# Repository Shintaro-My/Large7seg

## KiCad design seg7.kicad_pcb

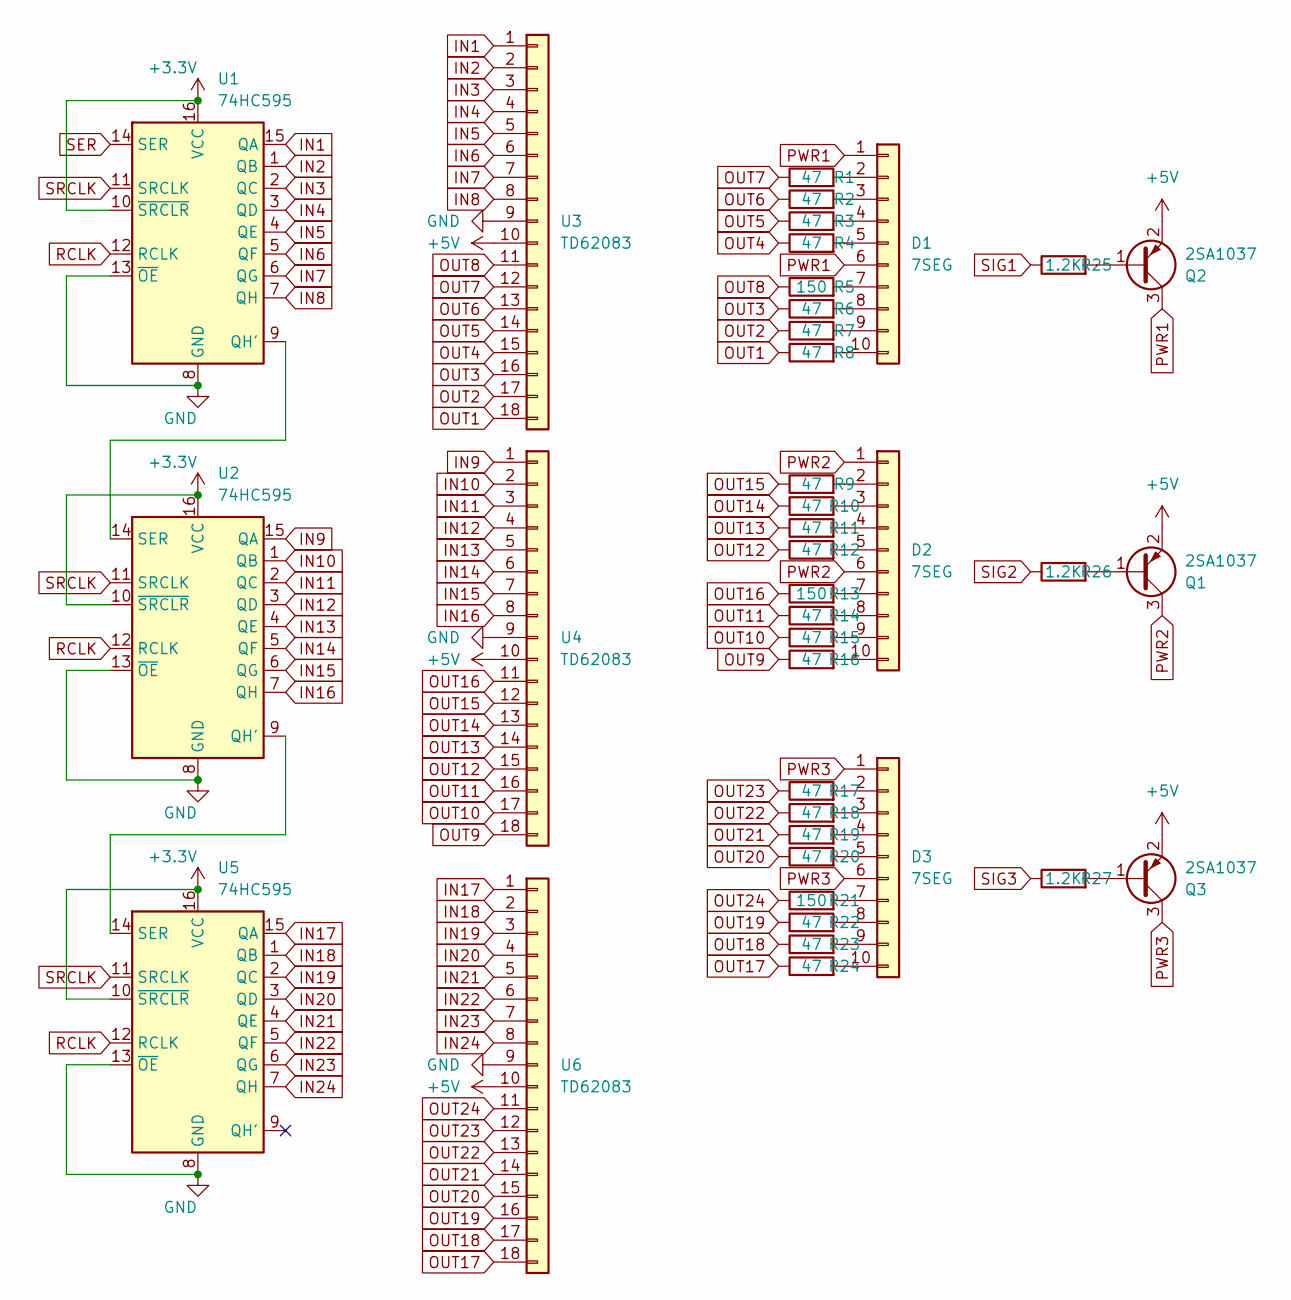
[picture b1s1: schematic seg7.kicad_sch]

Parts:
D1, D2, D3: 7SEG; 7SEG_GL9L15
Q1, Q2, Q3: 2SA1037; SOT-23
R1, R2, R3, R4, R6, R7, R8, R9, R10, R11, R12, R14, R15, R16, R17, R18, R19, R20, R22, R23, R24: 47; R_1206_3216Metric
R5, R13, R21: 150; R_1206_3216Metric
R25, R26, R27: 1.2K; R_0603_1608Metric_Pad0.98x0.95mm_HandSolder
U1, U2, U5: 74HC595; SOP16
U3, U4, U6: TD62083; SOIC-18W_7.5x11.6mm_P1.27mm

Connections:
+3.3V: U1.10 (~SRCLR), U1.16 (VCC), U2.10 (~SRCLR), U2.16 (VCC), U5.10 (~SRCLR), U5.16 (VCC)
+5V: Q1.2 (E), Q2.2 (E), Q3.2 (E), U3.10, U4.10, U6.10
GND: U1.8 (GND), U1.13 (~OE), U2.8 (GND), U2.13 (~OE), U3.9, U4.9, U5.8 (GND), U5.13 (~OE), U6.9
IN1: U1.15 (QA), U3.1
IN2: U1.1 (QB), U3.2
IN3: U1.2 (QC), U3.3
IN4: U1.3 (QD), U3.4
IN5: U1.4 (QE), U3.5
IN6: U1.5 (QF), U3.6
IN7: U1.6 (QG), U3.7
IN8: U1.7 (QH), U3.8
IN9: U2.15 (QA), U4.1
IN10: U2.1 (QB), U4.2
IN11: U2.2 (QC), U4.3
IN12: U2.3 (QD), U4.4
IN13: U2.4 (QE), U4.5
IN14: U2.5 (QF), U4.6
IN15: U2.6 (QG), U4.7
IN16: U2.7 (QH), U4.8
IN17: U5.15 (QA), U6.1
IN18: U5.1 (QB), U6.2
IN19: U5.2 (QC), U6.3
IN20: U5.3 (QD), U6.4
IN21: U5.4 (QE), U6.5
IN22: U5.5 (QF), U6.6
IN23: U5.6 (QG), U6.7
IN24: U5.7 (QH), U6.8
unnamed: D1.2, R1.2
unnamed: D1.3, R2.2
unnamed: D1.4, R3.2
unnamed: D1.5, R4.2
unnamed: D1.7, R5.2
unnamed: D1.8, R6.2
unnamed: D1.9, R7.2
unnamed: D1.10, R8.2
unnamed: D2.2, R9.2
unnamed: D2.3, R10.2
unnamed: D2.4, R11.2
unnamed: D2.5, R12.2
unnamed: D2.7, R13.2
unnamed: D2.8, R14.2
unnamed: D2.9, R15.2
unnamed: D2.10, R16.2
unnamed: D3.2, R17.2
unnamed: D3.3, R18.2
unnamed: D3.4, R19.2
unnamed: D3.5, R20.2
unnamed: D3.7, R21.2
unnamed: D3.8, R22.2
unnamed: D3.9, R23.2
unnamed: D3.10, R24.2
unnamed: Q1.1 (B), R26.2
unnamed: Q2.1 (B), R25.2
unnamed: Q3.1 (B), R27.2
unnamed: U1.9 (QH'), U2.14 (SER)
unnamed: U2.9 (QH'), U5.14 (SER)
OUT1: R8.1, U3.18
OUT2: R7.1, U3.17
OUT3: R6.1, U3.16
OUT4: R4.1, U3.15
OUT5: R3.1, U3.14
OUT6: R2.1, U3.13
OUT7: R1.1, U3.12
OUT8: R5.1, U3.11
OUT9: R16.1, U4.18
OUT10: R15.1, U4.17
OUT11: R14.1, U4.16
OUT12: R12.1, U4.15
OUT13: R11.1, U4.14
OUT14: R10.1, U4.13
OUT15: R9.1, U4.12
OUT16: R13.1, U4.11
OUT17: R24.1, U6.18
OUT18: R23.1, U6.17
OUT19: R22.1, U6.16
OUT20: R20.1, U6.15
OUT21: R19.1, U6.14
OUT22: R18.1, U6.13
OUT23: R17.1, U6.12
OUT24: R21.1, U6.11
PWR1: D1.1, D1.6, Q2.3 (C)
PWR2: D2.1, D2.6, Q1.3 (C)
PWR3: D3.1, D3.6, Q3.3 (C)
RCLK: U1.12 (RCLK), U2.12 (RCLK), U5.12 (RCLK)
SER: U1.14 (SER)
SIG1: R25.1
SIG2: R26.1
SIG3: R27.1
SRCLK: U1.11 (SRCLK), U2.11 (SRCLK), U5.11 (SRCLK)

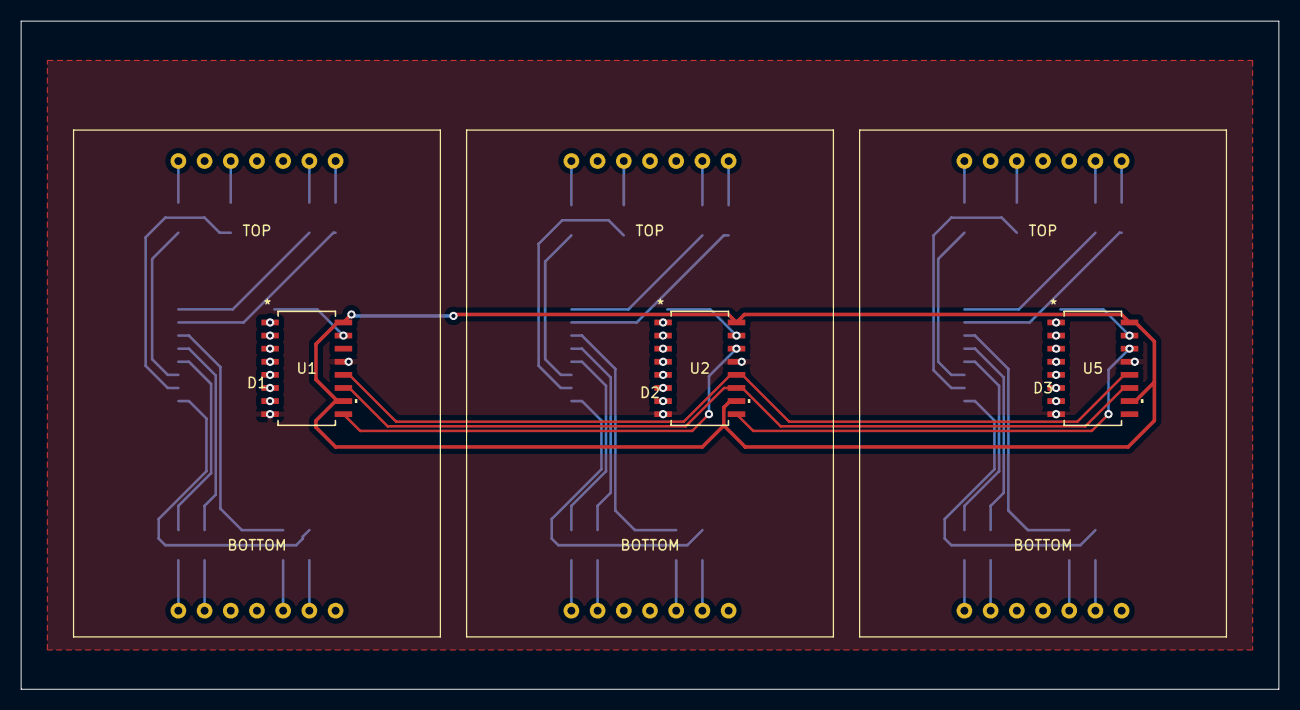
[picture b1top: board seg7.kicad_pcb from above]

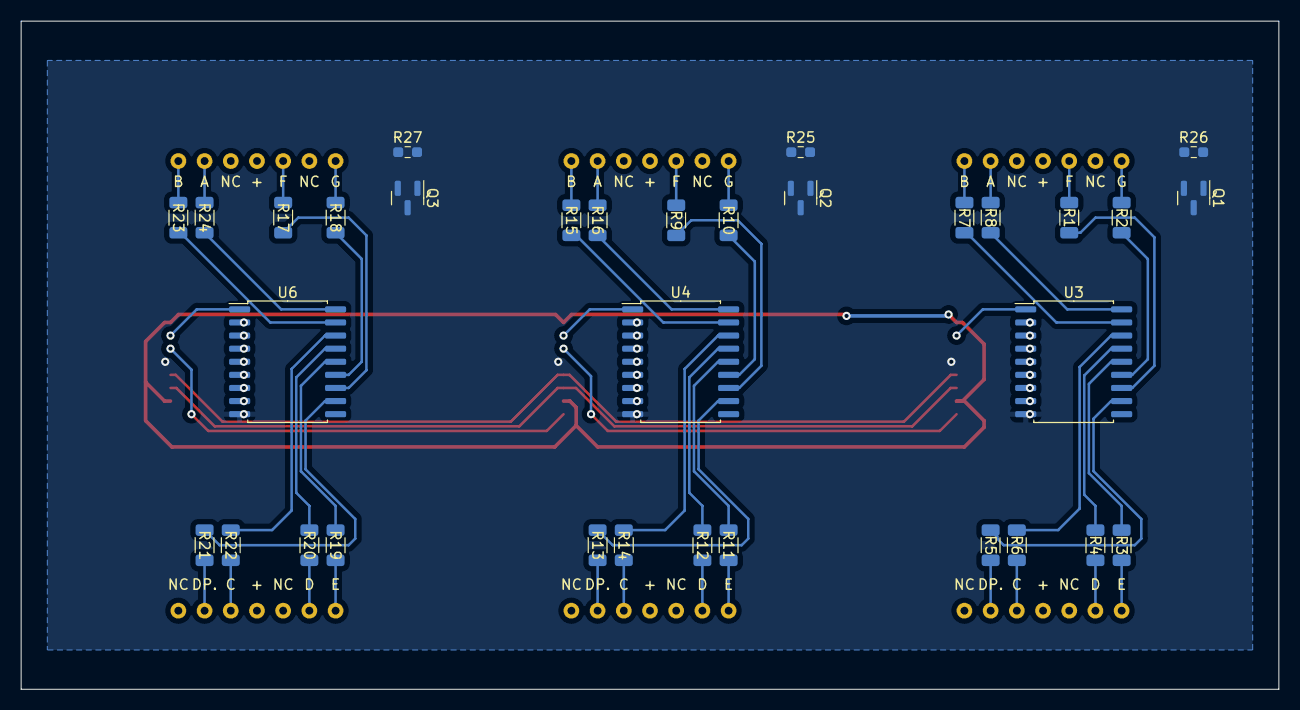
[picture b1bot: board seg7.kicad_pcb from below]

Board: 2 copper layers, 121.9 x 64.8 mm, 39 parts (33 on the bottom side), 85 nets.
